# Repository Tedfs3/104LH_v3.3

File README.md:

# 104LH_v3.3
# This is a left handed version of user null's keyboard design on the forum GeekHack. https://geekhack.org/index.php?topic=97883.0
# I have no idea what I'm doing and am just copying his design as best as possible while moving the numpad to the left side.
FreeRoute has been used to trace 99% of this PCB. Getting pointers on cleaning things up and just fixing odd routes has been a great help in learning how do things myself. Not close to trying to start something like this without the help of an auto router yet, maybe someday.
# v3.3.3 Prototype boards have been ordered. If they work properly, v3.3.3.1 will add support for Cherry MX Stabilizers.

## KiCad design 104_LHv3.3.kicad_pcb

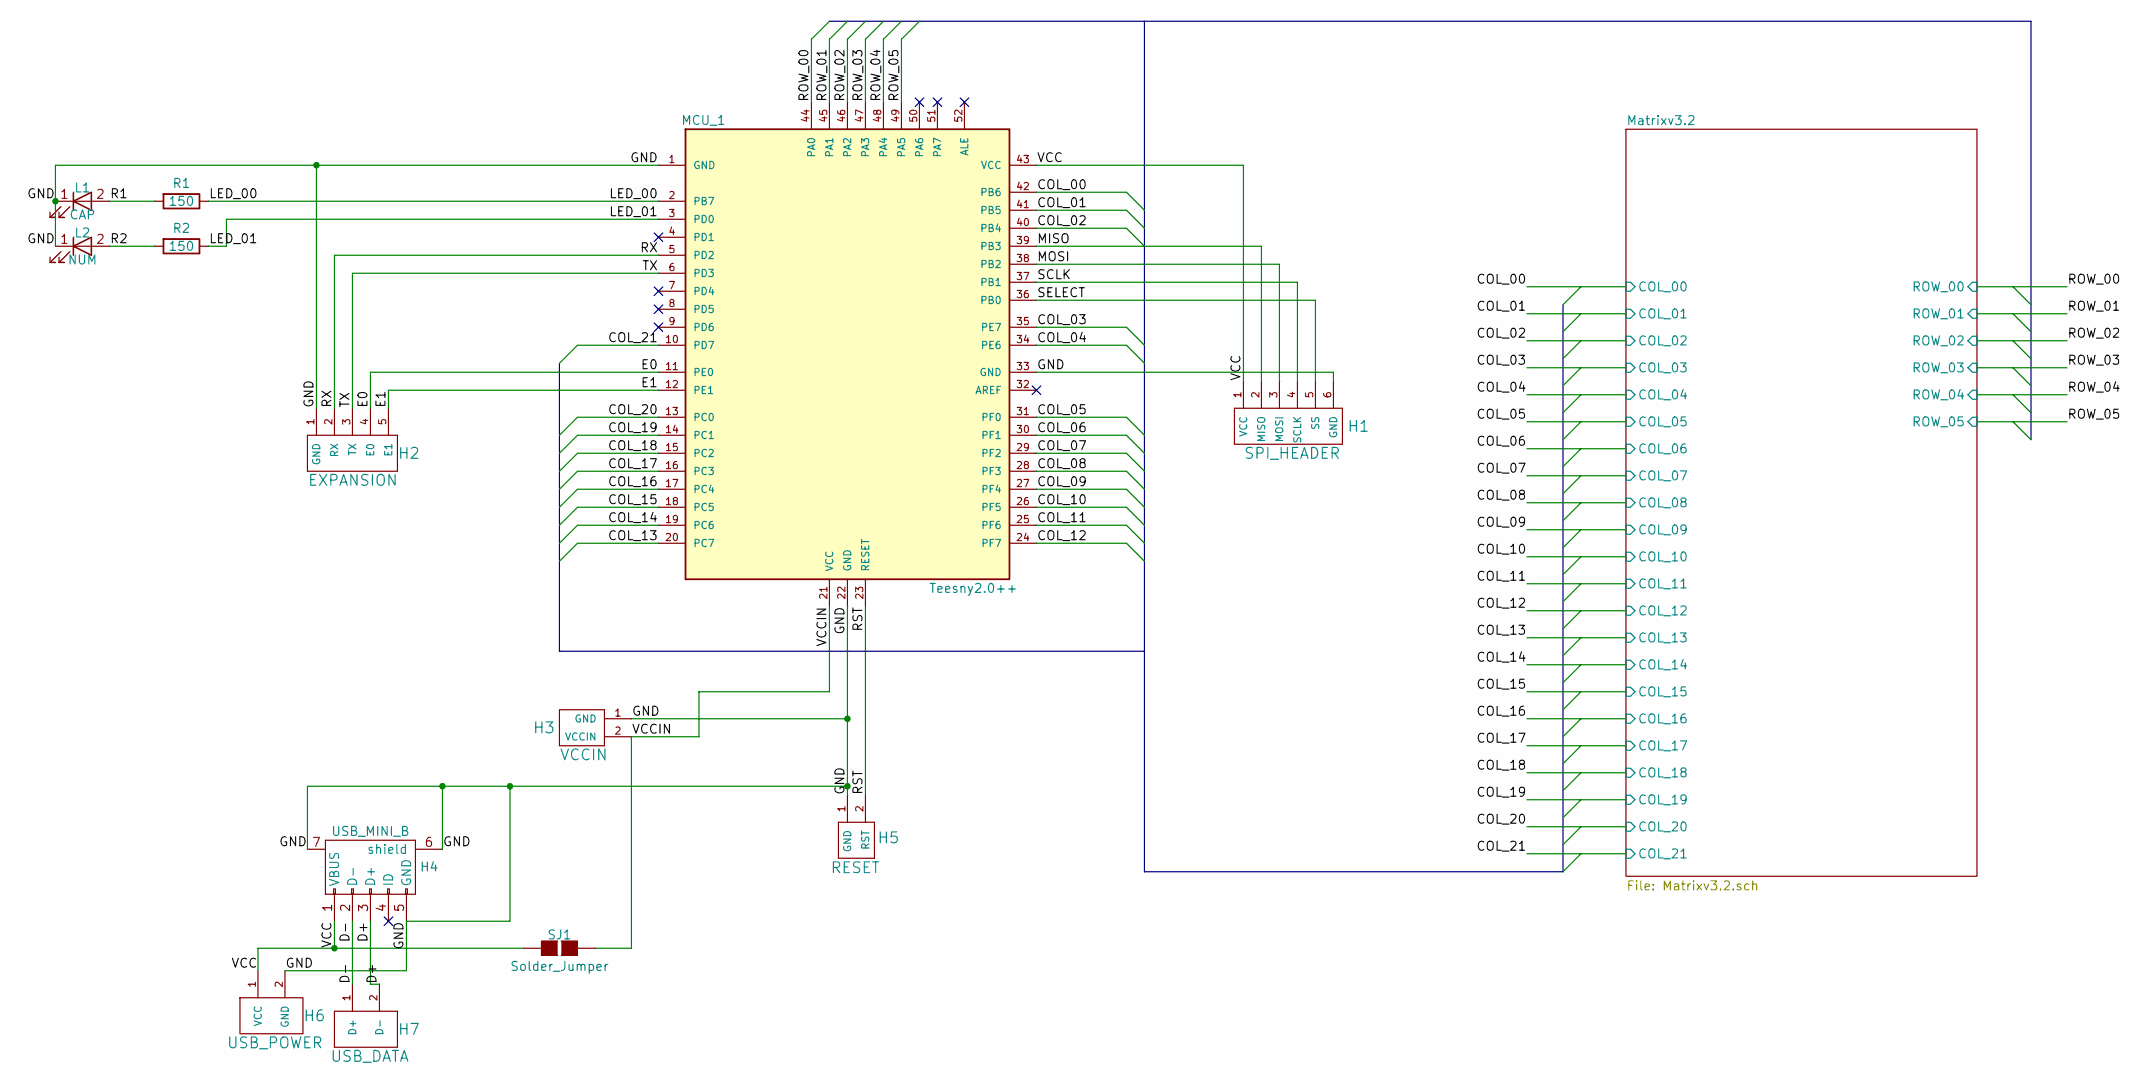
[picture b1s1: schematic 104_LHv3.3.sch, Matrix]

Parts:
H1: SPI_HEADER; SPI
H2: EXPANSION; Expansion
H3: VCCIN; USB_VCCIN
H4: USB_MINI_B; USB_Mini-B
H5: RESET; Reset
H6: USB_POWER; USB_Power
H7: USB_DATA; USB_Data
L1: CAP; LED_D3.0mm_FlatTop
L2: NUM; LED_D3.0mm_FlatTop
MCU_1: Teesny2.0++; TEENSY2.0++
R1, R2: 150; RESISTOR
SJ1: Solder_Jumper; USB_Jumper.1.70x2.0mm

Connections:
/COL_00: MCU_1.42 (PB6); also elsewhere on the board
/COL_01: MCU_1.41 (PB5); also elsewhere on the board
/COL_02: MCU_1.40 (PB4); also elsewhere on the board
/COL_03: MCU_1.35 (PE7); also elsewhere on the board
/COL_04: MCU_1.34 (PE6); also elsewhere on the board
/COL_05: MCU_1.31 (PF0); also elsewhere on the board
/COL_06: MCU_1.30 (PF1); also elsewhere on the board
/COL_07: MCU_1.29 (PF2); also elsewhere on the board
/COL_08: MCU_1.28 (PF3); also elsewhere on the board
/COL_09: MCU_1.27 (PF4); also elsewhere on the board
/COL_10: MCU_1.26 (PF5); also elsewhere on the board
/COL_11: MCU_1.25 (PF6); also elsewhere on the board
/COL_12: MCU_1.24 (PF7); also elsewhere on the board
/COL_13: MCU_1.20 (PC7); also elsewhere on the board
/COL_14: MCU_1.19 (PC6); also elsewhere on the board
/COL_15: MCU_1.18 (PC5); also elsewhere on the board
/COL_16: MCU_1.17 (PC4); also elsewhere on the board
/COL_17: MCU_1.16 (PC3); also elsewhere on the board
/COL_18: MCU_1.15 (PC2); also elsewhere on the board
/COL_19: MCU_1.14 (PC1); also elsewhere on the board
/COL_20: MCU_1.13 (PC0); also elsewhere on the board
/COL_21: MCU_1.10 (PD7); also elsewhere on the board
/D+: H4.3 (D+), H7.2 (D-)
/D-: H4.2 (D-), H7.1 (D+)
/E0: H2.4 (E0), MCU_1.11 (PE0)
/E1: H2.5 (E1), MCU_1.12 (PE1)
/GND: H1.6 (GND), H2.1 (GND), H3.1 (GND), H4.5 (GND), H4.6 (shield), H4.7, H5.1 (GND), H6.2 (GND), L1.1 (K), L2.1 (K), MCU_1.1 (GND), MCU_1.22 (GND), MCU_1.33 (GND)
/LED_00: MCU_1.2 (PB7), R1.1
/LED_01: MCU_1.3 (PD0), R2.1
/MISO: H1.2 (MISO), MCU_1.39 (PB3)
/MOSI: H1.3 (MOSI), MCU_1.38 (PB2)
/R1: L1.2 (A), R1.2
/R2: L2.2 (A), R2.2
/ROW_00: MCU_1.44 (PA0); also elsewhere on the board
/ROW_01: MCU_1.45 (PA1); also elsewhere on the board
/ROW_02: MCU_1.46 (PA2); also elsewhere on the board
/ROW_03: MCU_1.47 (PA3); also elsewhere on the board
/ROW_04: MCU_1.48 (PA4); also elsewhere on the board
/ROW_05: MCU_1.49 (PA5); also elsewhere on the board
/RST: H5.2 (RST), MCU_1.23 (RESET)
/RX: H2.2 (RX), MCU_1.5 (PD2)
/SCLK: H1.4 (SCLK), MCU_1.37 (PB1)
/SELECT: H1.5 (SS), MCU_1.36 (PB0)
/TX: H2.3 (TX), MCU_1.6 (PD3)

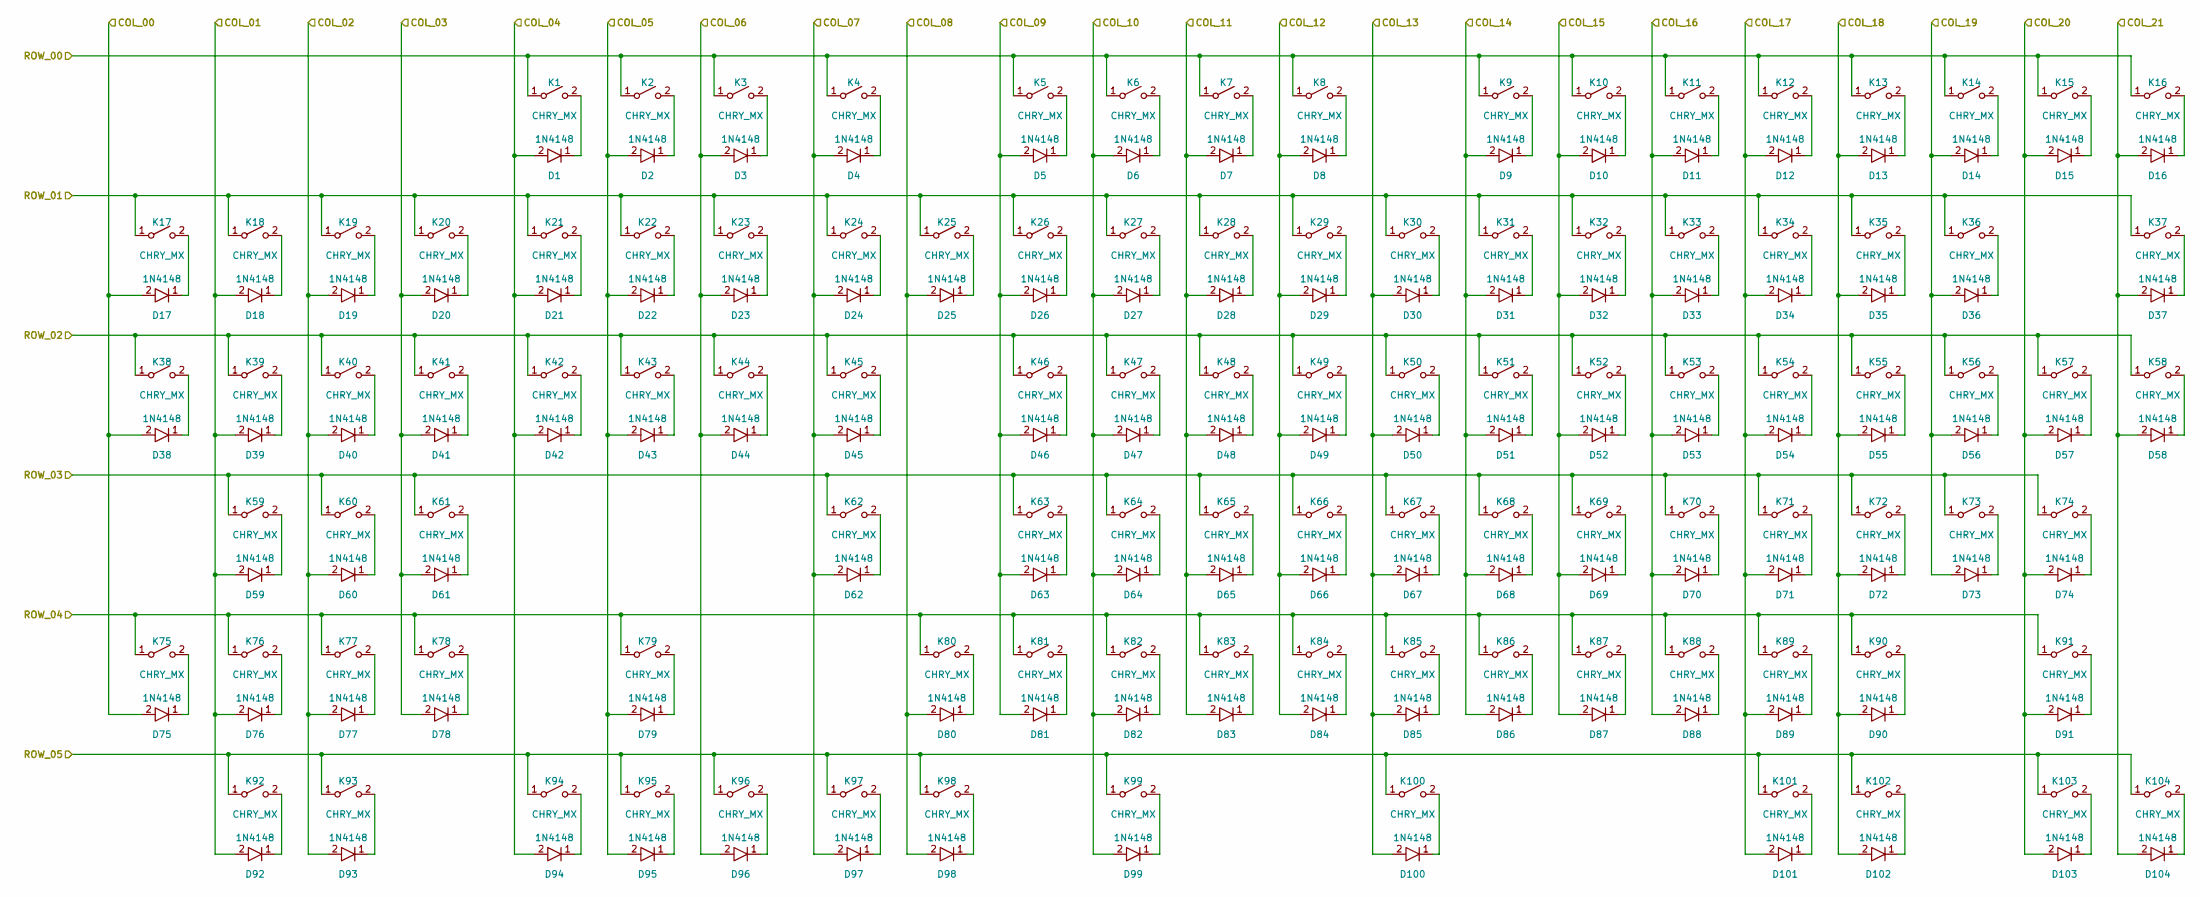
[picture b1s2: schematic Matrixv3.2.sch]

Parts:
D1, D2, D3, D4, D5, D6, D7, D8, D9, D10, D11, D12, D13, D14, D15, D16, D17, D18, D19, D20, D21, D22, D23, D24, D25, D26, D27, D28, D29, D30, D31, D32, D33, D34, D35, D36, D37, D38, D39, D40, D41, D42, D43, D44, D45, D46, D47, D48, D49, D50, D51, D52, D53, D54, D55, D56, D57, D58, D59, D60, D61, D62, D63, D64, D65, D66, D67, D68, D69, D70, D71, D72, D73, D74, D75, D76, D77, D78, D79, D80, D81, D82, D83, D84, D85, D86, D87, D88, D89, D90, D91, D92, D93, D94, D95, D96, D97, D98, D99, D100, D101, D102, D103, D104: 1N4148; D_axial
K1, K2, K3, K4, K5, K6, K7, K8, K9, K10, K11, K12, K13, K14, K15, K16, K17, K18, K19, K20, K21, K22, K23, K24, K25, K26, K27, K28, K29, K30, K31, K32, K33, K34, K35, K36, K39, K40, K41, K42, K43, K44, K46, K47, K48, K49, K50, K51, K52, K53, K54, K55, K56, K57, K59, K60, K61, K63, K64, K65, K66, K67, K68, K69, K70, K71, K72, K73, K76, K77, K78, K79, K81, K82, K83, K84, K85, K86, K87, K88, K89, K90, K92, K94, K95, K96: CHRY_MX; CHERRY_PLATE_100H
K37, K93: CHRY_MX; CHERRY_PLATE_200H
K38, K75: CHRY_MX; CHERRY_PLATE_200V
K45, K58: CHRY_MX; CHERRY_PLATE_150H
K62: CHRY_MX; CHERRY_PLATE_175H
K74, K80: CHRY_MX; CHERRY_PLATE_225H
K91: CHRY_MX; CHERRY_PLATE_275H
K97, K98, K99, K101, K102, K103, K104: CHRY_MX; CHERRY_PLATE_125H
K100: CHRY_MX; CHERRY_PLATE_625H

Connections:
/COL_00: D17.2 (A), D38.2 (A), D75.2 (A); also elsewhere on the board
/COL_01: D18.2 (A), D39.2 (A), D59.2 (A), D76.2 (A), D92.2 (A); also elsewhere on the board
/COL_02: D19.2 (A), D40.2 (A), D60.2 (A), D77.2 (A), D93.2 (A); also elsewhere on the board
/COL_03: D20.2 (A), D41.2 (A), D61.2 (A), D78.2 (A); also elsewhere on the board
/COL_04: D1.2 (A), D21.2 (A), D42.2 (A), D94.2 (A); also elsewhere on the board
/COL_05: D2.2 (A), D22.2 (A), D43.2 (A), D79.2 (A), D95.2 (A); also elsewhere on the board
/COL_06: D3.2 (A), D23.2 (A), D44.2 (A), D96.2 (A); also elsewhere on the board
/COL_07: D4.2 (A), D24.2 (A), D45.2 (A), D62.2 (A), D97.2 (A); also elsewhere on the board
/COL_08: D25.2 (A), D80.2 (A), D98.2 (A); also elsewhere on the board
/COL_09: D5.2 (A), D26.2 (A), D46.2 (A), D63.2 (A), D81.2 (A); also elsewhere on the board
/COL_10: D6.2 (A), D27.2 (A), D47.2 (A), D64.2 (A), D82.2 (A), D99.2 (A); also elsewhere on the board
/COL_11: D7.2 (A), D28.2 (A), D48.2 (A), D65.2 (A), D83.2 (A); also elsewhere on the board
/COL_12: D8.2 (A), D29.2 (A), D49.2 (A), D66.2 (A), D84.2 (A); also elsewhere on the board
/COL_13: D30.2 (A), D50.2 (A), D67.2 (A), D85.2 (A), D100.2 (A); also elsewhere on the board
/COL_14: D9.2 (A), D31.2 (A), D51.2 (A), D68.2 (A), D86.2 (A); also elsewhere on the board
/COL_15: D10.2 (A), D32.2 (A), D52.2 (A), D69.2 (A), D87.2 (A); also elsewhere on the board
/COL_16: D11.2 (A), D33.2 (A), D53.2 (A), D70.2 (A), D88.2 (A); also elsewhere on the board
/COL_17: D12.2 (A), D34.2 (A), D54.2 (A), D71.2 (A), D89.2 (A), D101.2 (A); also elsewhere on the board
/COL_18: D13.2 (A), D35.2 (A), D55.2 (A), D72.2 (A), D90.2 (A), D102.2 (A); also elsewhere on the board
/COL_19: D14.2 (A), D36.2 (A), D56.2 (A), D73.2 (A); also elsewhere on the board
/COL_20: D15.2 (A), D57.2 (A), D74.2 (A), D91.2 (A), D103.2 (A); also elsewhere on the board
/COL_21: D16.2 (A), D37.2 (A), D58.2 (A), D104.2 (A); also elsewhere on the board
/ROW_00: K1.1 (A), K2.1 (A), K3.1 (A), K4.1 (A), K5.1 (A), K6.1 (A), K7.1 (A), K8.1 (A), K9.1 (A), K10.1 (A), K11.1 (A), K12.1 (A), K13.1 (A), K14.1 (A), K15.1 (A), K16.1 (A); also elsewhere on the board
/ROW_01: K17.1 (A), K18.1 (A), K19.1 (A), K20.1 (A), K21.1 (A), K22.1 (A), K23.1 (A), K24.1 (A), K25.1 (A), K26.1 (A), K27.1 (A), K28.1 (A), K29.1 (A), K30.1 (A), K31.1 (A), K32.1 (A), K33.1 (A), K34.1 (A), K35.1 (A), K36.1 (A), K37.1 (A); also elsewhere on the board
/ROW_02: K38.1 (A), K39.1 (A), K40.1 (A), K41.1 (A), K42.1 (A), K43.1 (A), K44.1 (A), K45.1 (A), K46.1 (A), K47.1 (A), K48.1 (A), K49.1 (A), K50.1 (A), K51.1 (A), K52.1 (A), K53.1 (A), K54.1 (A), K55.1 (A), K56.1 (A), K57.1 (A), K58.1 (A); also elsewhere on the board
/ROW_03: K59.1 (A), K60.1 (A), K61.1 (A), K62.1 (A), K63.1 (A), K64.1 (A), K65.1 (A), K66.1 (A), K67.1 (A), K68.1 (A), K69.1 (A), K70.1 (A), K71.1 (A), K72.1 (A), K73.1 (A), K74.1 (A); also elsewhere on the board
/ROW_04: K75.1 (A), K76.1 (A), K77.1 (A), K78.1 (A), K79.1 (A), K80.1 (A), K81.1 (A), K82.1 (A), K83.1 (A), K84.1 (A), K85.1 (A), K86.1 (A), K87.1 (A), K88.1 (A), K89.1 (A), K90.1 (A), K91.1 (A); also elsewhere on the board
/ROW_05: K92.1 (A), K93.1 (A), K94.1 (A), K95.1 (A), K96.1 (A), K97.1 (A), K98.1 (A), K99.1 (A), K100.1 (A), K101.1 (A), K102.1 (A), K103.1 (A), K104.1 (A); also elsewhere on the board
unnamed: D1.1 (K), K1.2 (B)
unnamed: D2.1 (K), K2.2 (B)
unnamed: D3.1 (K), K3.2 (B)
unnamed: D4.1 (K), K4.2 (B)
unnamed: D5.1 (K), K5.2 (B)
unnamed: D6.1 (K), K6.2 (B)
unnamed: D7.1 (K), K7.2 (B)
unnamed: D8.1 (K), K8.2 (B)
unnamed: D9.1 (K), K9.2 (B)
unnamed: D10.1 (K), K10.2 (B)
unnamed: D11.1 (K), K11.2 (B)
unnamed: D12.1 (K), K12.2 (B)
unnamed: D13.1 (K), K13.2 (B)
unnamed: D14.1 (K), K14.2 (B)
unnamed: D15.1 (K), K15.2 (B)
unnamed: D16.1 (K), K16.2 (B)
unnamed: D17.1 (K), K17.2 (B)
unnamed: D18.1 (K), K18.2 (B)
unnamed: D19.1 (K), K19.2 (B)
unnamed: D20.1 (K), K20.2 (B)
unnamed: D21.1 (K), K21.2 (B)
unnamed: D22.1 (K), K22.2 (B)
unnamed: D23.1 (K), K23.2 (B)
unnamed: D24.1 (K), K24.2 (B)
unnamed: D25.1 (K), K25.2 (B)
unnamed: D26.1 (K), K26.2 (B)
unnamed: D27.1 (K), K27.2 (B)
unnamed: D28.1 (K), K28.2 (B)
unnamed: D29.1 (K), K29.2 (B)
unnamed: D30.1 (K), K30.2 (B)
unnamed: D31.1 (K), K31.2 (B)
unnamed: D32.1 (K), K32.2 (B)
unnamed: D33.1 (K), K33.2 (B)
unnamed: D34.1 (K), K34.2 (B)
unnamed: D35.1 (K), K35.2 (B)
unnamed: D36.1 (K), K36.2 (B)
unnamed: D37.1 (K), K37.2 (B)
unnamed: D38.1 (K), K38.2 (B)
unnamed: D39.1 (K), K39.2 (B)
unnamed: D40.1 (K), K40.2 (B)
unnamed: D41.1 (K), K41.2 (B)
unnamed: D42.1 (K), K42.2 (B)
unnamed: D43.1 (K), K43.2 (B)
unnamed: D44.1 (K), K44.2 (B)
unnamed: D45.1 (K), K45.2 (B)
unnamed: D46.1 (K), K46.2 (B)
unnamed: D47.1 (K), K47.2 (B)
unnamed: D48.1 (K), K48.2 (B)
unnamed: D49.1 (K), K49.2 (B)
unnamed: D50.1 (K), K50.2 (B)
unnamed: D51.1 (K), K51.2 (B)
unnamed: D52.1 (K), K52.2 (B)
unnamed: D53.1 (K), K53.2 (B)
unnamed: D54.1 (K), K54.2 (B)
unnamed: D55.1 (K), K55.2 (B)
unnamed: D56.1 (K), K56.2 (B)
unnamed: D57.1 (K), K57.2 (B)
unnamed: D58.1 (K), K58.2 (B)
unnamed: D59.1 (K), K59.2 (B)
unnamed: D60.1 (K), K60.2 (B)
unnamed: D61.1 (K), K61.2 (B)
unnamed: D62.1 (K), K62.2 (B)
unnamed: D63.1 (K), K63.2 (B)
unnamed: D64.1 (K), K64.2 (B)
unnamed: D65.1 (K), K65.2 (B)
unnamed: D66.1 (K), K66.2 (B)
unnamed: D67.1 (K), K67.2 (B)
unnamed: D68.1 (K), K68.2 (B)
unnamed: D69.1 (K), K69.2 (B)
unnamed: D70.1 (K), K70.2 (B)
unnamed: D71.1 (K), K71.2 (B)
unnamed: D72.1 (K), K72.2 (B)
unnamed: D73.1 (K), K73.2 (B)
unnamed: D74.1 (K), K74.2 (B)
unnamed: D75.1 (K), K75.2 (B)
unnamed: D76.1 (K), K76.2 (B)
unnamed: D77.1 (K), K77.2 (B)
unnamed: D78.1 (K), K78.2 (B)
unnamed: D79.1 (K), K79.2 (B)
unnamed: D80.1 (K), K80.2 (B)
unnamed: D81.1 (K), K81.2 (B)
unnamed: D82.1 (K), K82.2 (B)
unnamed: D83.1 (K), K83.2 (B)
unnamed: D84.1 (K), K84.2 (B)
unnamed: D85.1 (K), K85.2 (B)
unnamed: D86.1 (K), K86.2 (B)
unnamed: D87.1 (K), K87.2 (B)
unnamed: D88.1 (K), K88.2 (B)
unnamed: D89.1 (K), K89.2 (B)
unnamed: D90.1 (K), K90.2 (B)
unnamed: D91.1 (K), K91.2 (B)
unnamed: D92.1 (K), K92.2 (B)
unnamed: D93.1 (K), K93.2 (B)
unnamed: D94.1 (K), K94.2 (B)
unnamed: D95.1 (K), K95.2 (B)
unnamed: D96.1 (K), K96.2 (B)
unnamed: D97.1 (K), K97.2 (B)
unnamed: D98.1 (K), K98.2 (B)
unnamed: D99.1 (K), K99.2 (B)
unnamed: D100.1 (K), K100.2 (B)
unnamed: D101.1 (K), K101.2 (B)
unnamed: D102.1 (K), K102.2 (B)
unnamed: D103.1 (K), K103.2 (B)
unnamed: D104.1 (K), K104.2 (B)

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
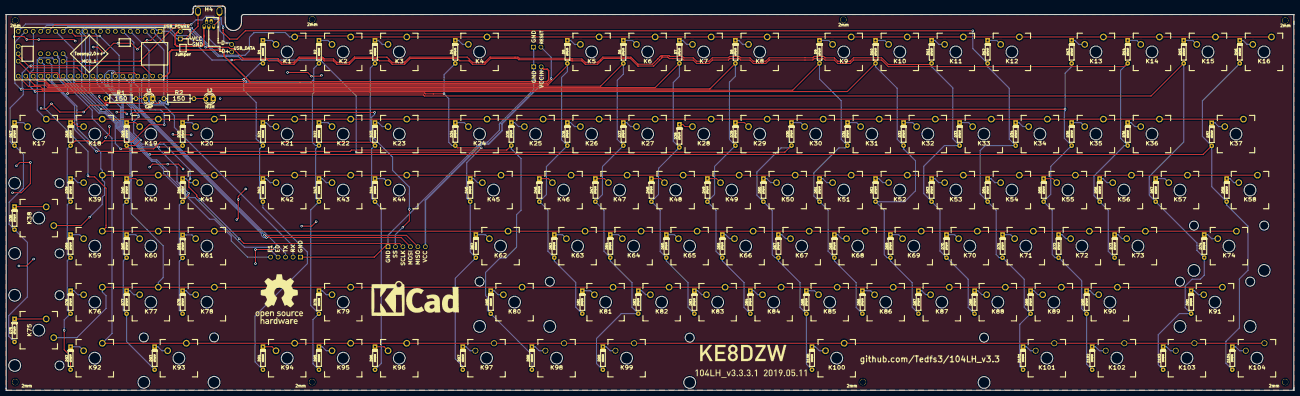
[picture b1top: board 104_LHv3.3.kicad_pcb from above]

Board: 2 copper layers, 437.8 x 130.6 mm, 242 parts (0 on the bottom side), 149 nets.

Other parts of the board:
01, 02, 03, 04, 05, 06, 07, 08: 2mm; 2mm_Hole
2.0u: 2.0u; Mx_Stab_200
2.0u1, 2.0u2: Stabilizer; Mx_Stab_200
225: >VALUE; Mx_Stab_225
Bottom: LOGO; logoR
LEnter: >VALUE; Mx_Stab_225
LShift: >VALUE; Mx_Stab_275
Space: >VALUE; Mx_Stab_625
Top: LOGO; logo
VIB: LOGO; version.infoR
VIF: LOGO; version.info
kilogo: LOGO; kilogo
oshw: LOGO; oshw

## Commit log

2019-04-20 Fixed backwards LEDs
2019-04-20 Fixed backwards LEDs.
2019-04-20 Update README.md
    General comments.
2019-04-20 Clean up LED text
2019-04-20 Jumper picture added
2019-04-20 Cleaning up tracks
2019-04-27 Adding support for Stabilizers.
    Prototype boards have been ordered. If they work as intended, this version will be the next batch ordered with Cherry MX Stabilizer support.
2019-04-27 v3.3.3 Backup
    v3.3.3 Backup before support for Cherry MX Stabilizers is being added to v 3.3.3.1
2019-04-27 Clean up. Support for Cherry MX Stabilizers.
2019-04-28 Adding more stabilizers
2019-04-28 Stabilizers added.
2019-05-11 More updates
    Adding support for stabilizers. Graphics added and a backup copy of the unrouted board.
2019-05-11 Update Footprints
    Updated cherry footprints. Added separate Log and Version footprints. Open Source Hardware and KiCad logos added.
2019-06-02 Tweaks in Stabs
2019-06-09 Updated Changes
